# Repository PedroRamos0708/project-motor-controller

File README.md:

# Projeto de Controle com Microcontrolador

## Descrição
Este projeto foi desenvolvido como parte de um desafio de hardware.
O objetivo é criar um sistema embarcado capaz de:
* Receber um sinal externo de 12 V ativo em nível baixo.
* Acionar um motor DC 5 V / 1 A por 10 segundos.
* Enviar mensagens de status via UART RS232.
* Ser alimentado por uma fonte de 9 a 24 VDC, com proteções contra inversão de polaridade e surtos.

## Especificações de Hardware
* Microcontrolador: ATmega328P + botão de reset.
* Fonte de alimentação: regulador LM2596 (9–24 VDC para 5 V).
* Motor: 5 V / 1 A, acionado via MOSFET canal N, com fusível de proteção.
* Proteções:
  * Fusível resetável (PTC).
  * Diodo Schottky (SS34).
  * Diodo TVS (SMBJ33A).
* Interface de entrada: optoacoplador para isolamento do sinal de 12 V.
* Comunicação serial: MAX3232 para RS232.
* Sinalização de placa energizada: LED

## Firmware
O firmware em C/C++ (pronto para compilação no ARDUINO IDE) realiza:
1. Leitura do sinal externo via optoacoplador.
2. Acionamento do motor por 10 segundos.
3. Envio de mensagens de status na UART.

## Arquivos Gerados
* Esquemático em PDF.
* PCB desenhada no KiCad 9.
* Arquivos Gerber e Drill files para fabricação.
* Pick and Place (PnP) para montagem.
* BOM (Bill of Materials) para compra dos componentes.
* Arquivos de projeto editáveis da placa e esquematico (.kicad_pcd e _sch)

## Como usar
1. Alimente a placa com 9 a 24 VDC no conector J1 (pino interno VCC e externo GND) através de fonte externa;
2. Conecte o sinal externo de 12 V no borne J3 (pino 1 : GND, pino 2 : 12V) para habilitação do motor;
3. Conecte o motor DC 5 V / 1 A no borne J4 (pino 1 : +, pino 2 : GND);
4. Utilize a porta RS232 (Conector db9 J2) para monitorar as mensagens do sistema.

## Tecnologias Utilizadas
* KiCad 9 → desenvolvimento do esquemático e PCB.
* Arduino IDE → programação do microcontrolador.

## Autor
Projeto desenvolvido por Pedro Henrique Ramos, Engenheiro de Controle e Automação e técnico em eletroeletrônica.

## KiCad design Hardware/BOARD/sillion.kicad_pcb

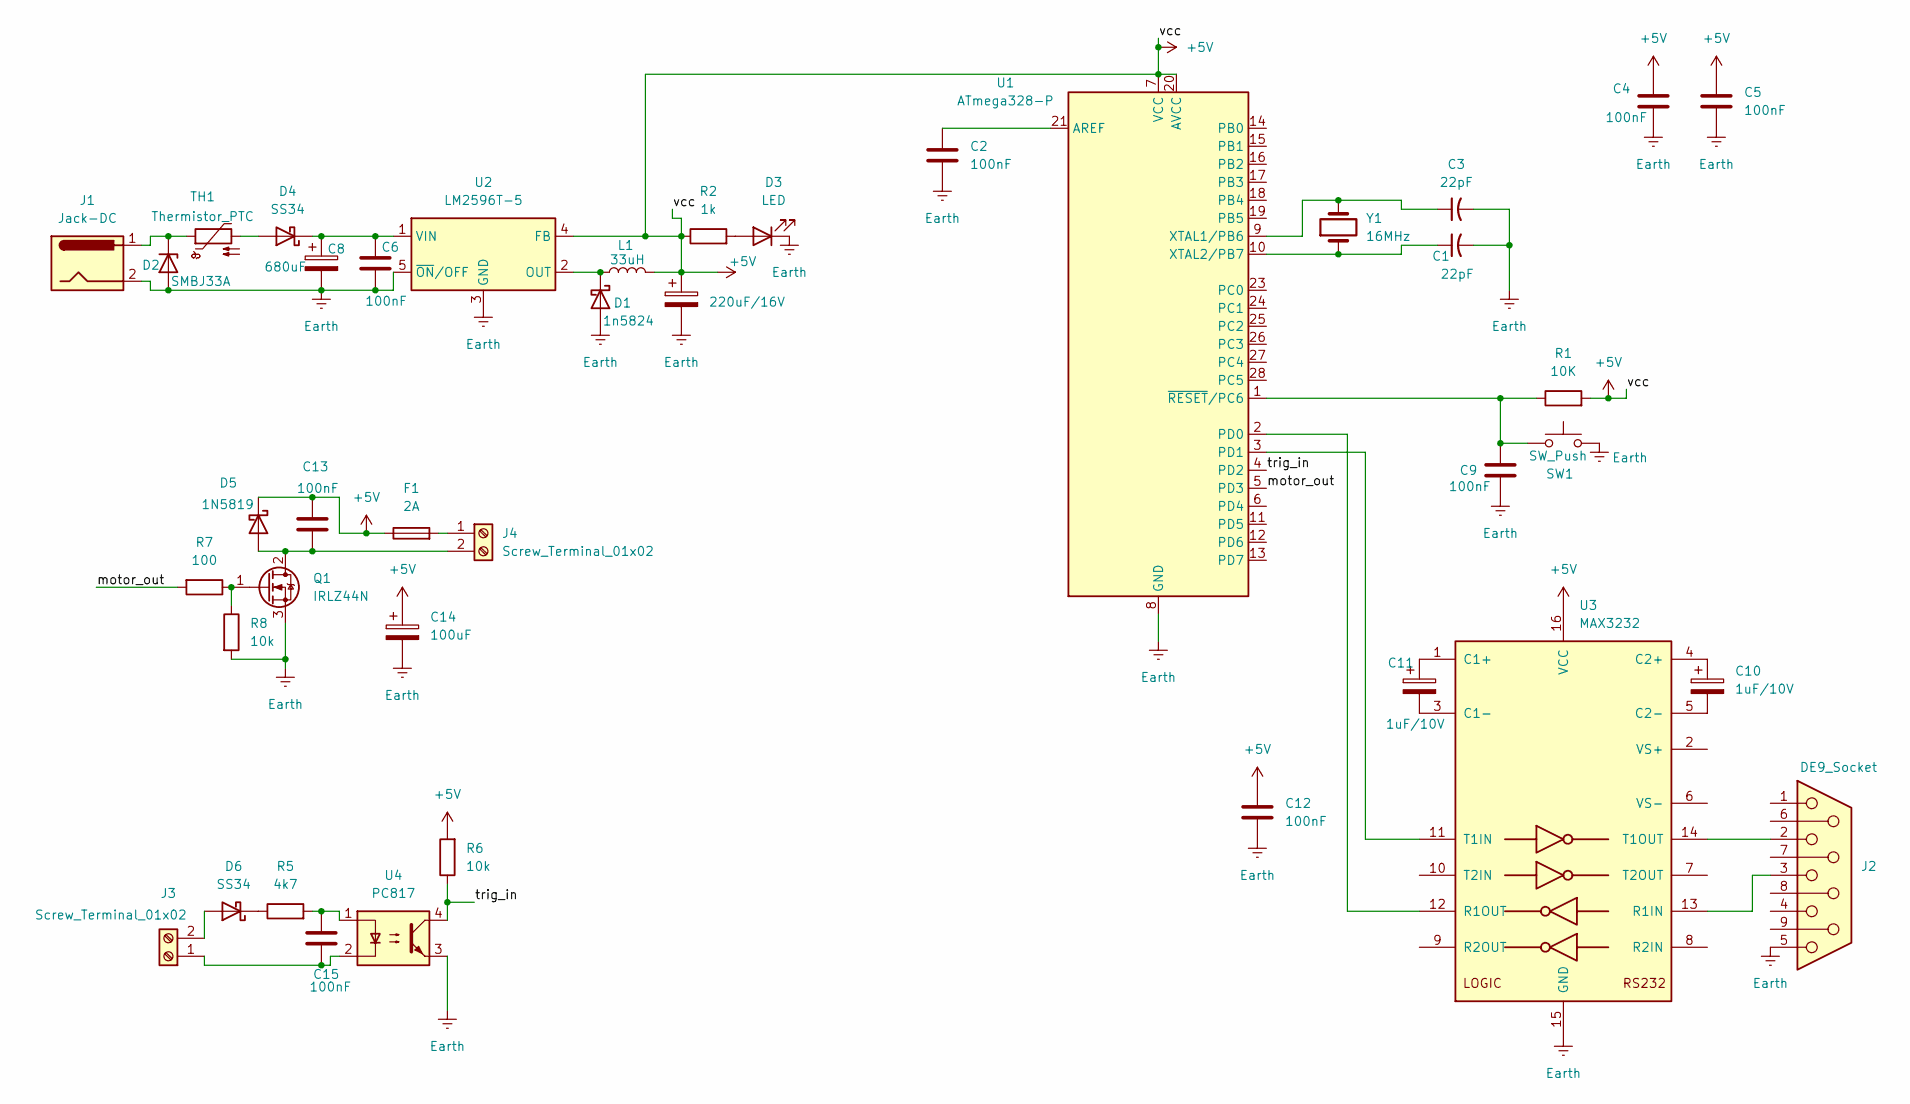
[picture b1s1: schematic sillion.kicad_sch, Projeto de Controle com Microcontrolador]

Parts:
C1, C3: 22pF; C_Disc_D4.3mm_W1.9mm_P5.00mm
C2, C4, C5, C6, C9, C12, C13, C15: 100nF; C_Disc_D4.3mm_W1.9mm_P5.00mm
C7: 220uF/16V; CP_Radial_D8.0mm_P5.00mm
C8: 680uF; CP_Radial_D13.0mm_P7.50mm
C10, C11: 1uF/10V; C_0805_2012Metric
C14: 100uF; CP_Radial_D5.0mm_P2.50mm
D1: 1n5824; TO-220-2_Vertical
D2: SMBJ33A; D_SMB
D3: LED; LED_D5.0mm
D4, D6: SS34; D_SMA
D5: 1N5819; D_DO-41_SOD81_P10.16mm_Horizontal
F1: 2A; Fuseholder_Clip-5x20mm_Bel_FC-203-22_Lateral_P17.80x5.00mm_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
J1: Jack-DC; BarrelJack_Horizontal
J2: DE9_Socket; DSUB-9_Socket_Horizontal_P2.77x2.84mm_EdgePinOffset4.94mm_H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
J3, J4: Screw_Terminal_01x02; TerminalBlock_Altech_AK300-2_P5.00mm
L1: 33uH; L_Radial_D12.5mm_P7.00mm_Fastron_09HCP
Q1: IRLZ44N; TO-220-3_Vertical
R1: 10K; R_Axial_DIN0207_L6.3mm_D2.5mm_P10.16mm_Horizontal
R2: 1k; R_Axial_DIN0207_L6.3mm_D2.5mm_P10.16mm_Horizontal
R5: 4k7; R_Axial_DIN0207_L6.3mm_D2.5mm_P10.16mm_Horizontal
R6, R8: 10k; R_Axial_DIN0207_L6.3mm_D2.5mm_P10.16mm_Horizontal
R7: 100; R_Axial_DIN0207_L6.3mm_D2.5mm_P10.16mm_Horizontal
SW1: SW_Push; SW_PUSH_6mm_H5mm
TH1: Thermistor_PTC; Fuse_BelFuse_0ZRE0025FF_L9.6mm_W3.8mm
U1: ATmega328-P; DIP-28_W7.62mm
U2: LM2596T-5; TO-220-5_P3.4x3.7mm_StaggerOdd_Lead3.8mm_Vertical
U3: MAX3232; JEITA_SOIC-16_3.9x9.9mm_P1.27mm
U4: PC817; DIP-4_W7.62mm
Y1: 16MHz; Crystal_HC49-4H_Vertical

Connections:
+5V: C4.1, C5.1, C7.1, C12.1, C13.1, C14.1, D5.1 (K), F1.1, L1.2, R1.2, R2.1, R6.2, U1.7 (VCC), U1.20 (AVCC), U2.4 (FB), U3.16 (VCC)
/motor_out: R7.2, U1.5 (PD3)
/trig_in: R6.1, U1.4 (PD2), U4.4
Earth: C1.2, C2.2, C3.2, C4.2, C5.2, C6.2, C7.2, C8.2, C9.2, C12.2, C14.2, D1.2 (A), D2.2 (A), D3.1 (K), J1.2, J2.5, Q1.3 (S), R8.2, SW1.2, U1.8 (GND), U1.22 (GND), U2.3 (GND), U2.5 (~ON/OFF), U3.15 (GND), U4.3
unnamed: C15.1, R5.2, U4.1
unnamed: D1.1 (K), L1.1, U2.2 (OUT)
unnamed: D2.1 (K), J1.1, TH1.1
unnamed: D3.2 (A), R2.2
unnamed: D4.2 (A), TH1.2
unnamed: C6.1, C8.1, D4.1 (K), U2.1 (VIN)
unnamed: C13.2, D5.2 (A), J4.2, Q1.2 (D)
unnamed: D6.2 (A), J3.2
unnamed: D6.1 (K), R5.1
unnamed: C15.2, J3.1, U4.2
unnamed: F1.2, J4.1
unnamed: Q1.1 (G), R7.1, R8.1
unnamed: C2.1, U1.21 (AREF)
unnamed: U1.2 (PD0), U3.12 (R1OUT)
unnamed: U1.3 (PD1), U3.11 (T1IN)
unnamed: C3.1, U1.9 (XTAL1/PB6), Y1.2
unnamed: C1.1, U1.10 (XTAL2/PB7), Y1.1
unnamed: C9.1, R1.1, SW1.1, U1.1 (~RESET/PC6)
unnamed: C11.1, U3.1 (C1+)
unnamed: C11.2, U3.3 (C1-)
unnamed: C10.1, U3.4 (C2+)
unnamed: C10.2, U3.5 (C2-)
unnamed: J2.3, U3.13 (R1IN)
unnamed: J2.2, U3.14 (T1OUT)

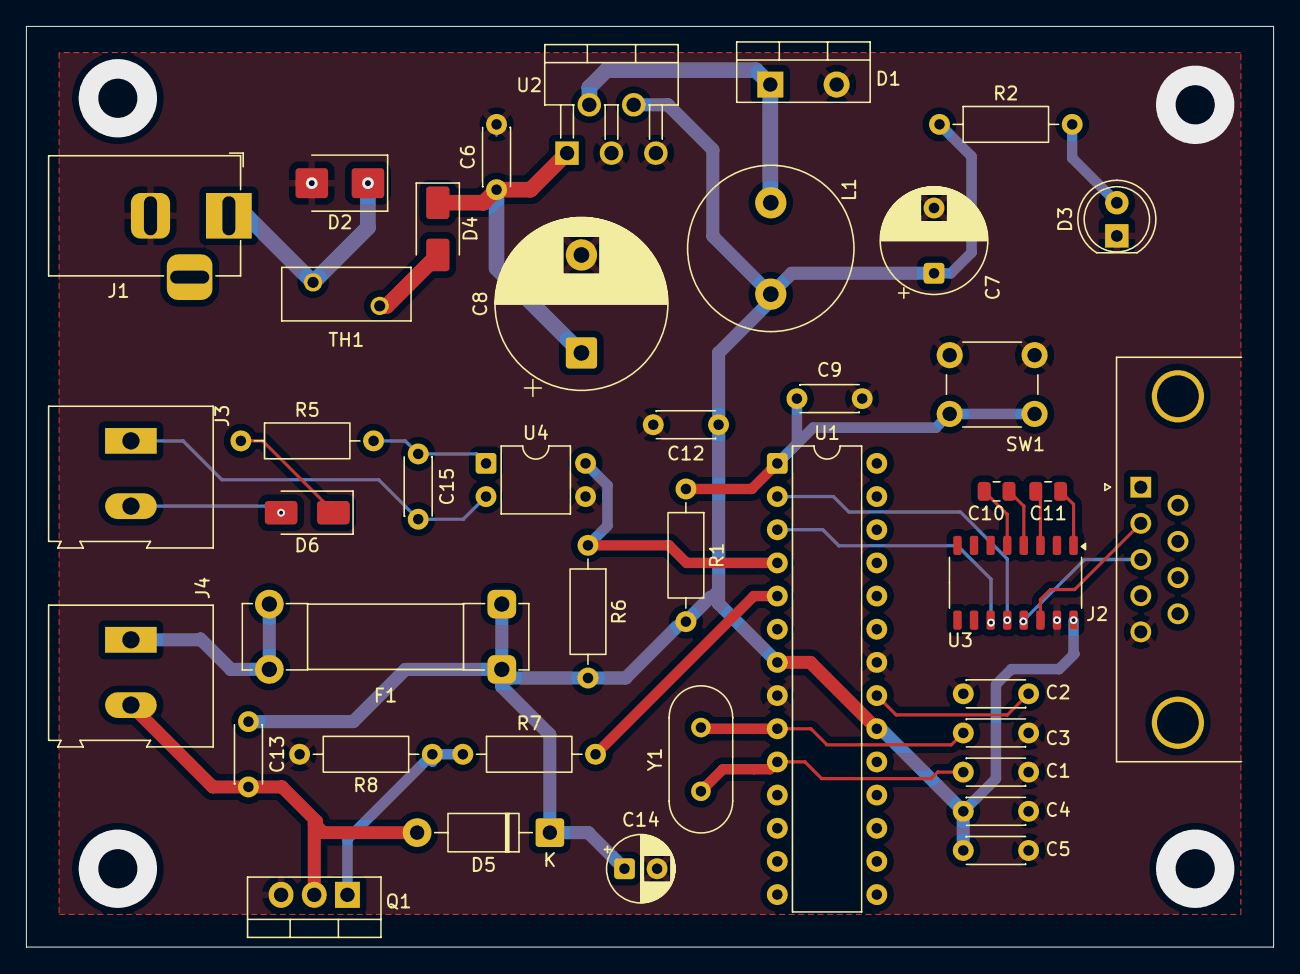
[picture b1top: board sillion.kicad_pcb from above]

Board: 2 copper layers, 95.5 x 70.5 mm, 41 parts (0 on the bottom side), 28 nets.

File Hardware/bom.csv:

"Reference","Qty","Value","DNP","Exclude from BOM","Exclude from Board","Footprint","Datasheet"
"C1,C3","2","22pF","","","","Capacitor_THT:C_Disc_D4.3mm_W1.9mm_P5.00mm",""
"C2,C4,C5,C6,C9,C12,C13,C15","8","100nF","","","","Capacitor_THT:C_Disc_D4.3mm_W1.9mm_P5.00mm","~"
"C7","1","220uF/16V","","","","Capacitor_THT:CP_Radial_D8.0mm_P5.00mm","~"
"C8","1","680uF","","","","Capacitor_THT:CP_Radial_D13.0mm_P7.50mm","~"
"C10,C11","2","1uF/10V","","","","Capacitor_SMD:C_0805_2012Metric","~"
"C14","1","100uF","","","","Capacitor_THT:CP_Radial_D5.0mm_P2.50mm","~"
"D1","1","1n5824","","","","Package_TO_SOT_THT:TO-220-2_Vertical","~"
"D2","1","SMBJ33A","","","","Diode_SMD:D_SMB","~"
"D3","1","LED","","","","LED_THT:LED_D5.0mm","~"
"D4,D6","2","SS34","","","","Diode_SMD:D_SMA","https://www.vishay.com/docs/88751/ss32.pdf"
"D5","1","1N5819","","","","Diode_THT:D_DO-41_SOD81_P10.16mm_Horizontal","http://www.vishay.com/docs/88525/1n5817.pdf"
"F1","1","2A","","","","Fuse:Fuseholder_Clip-5x20mm_Bel_FC-203-22_Lateral_P17.80x5.00mm_D1.17mm_Horizontal","~"
"J1","1","Jack-DC","","","","Connector_BarrelJack:BarrelJack_Horizontal","~"
"J2","1","DE9_Socket","","","","Connector_Dsub:DSUB-9_Socket_Horizontal_P2.77x2.84mm_EdgePinOffset4.94mm_Housed_MountingHolesOffset4.94mm","~"
"J3,J4","2","Screw_Terminal_01x02","","","","TerminalBlock:TerminalBlock_Altech_AK300-2_P5.00mm","~"
"L1","1","33uH","","","","Inductor_THT:L_Radial_D12.5mm_P7.00mm_Fastron_09HCP","~"
"Q1","1","IRLZ44N","","","","Package_TO_SOT_THT:TO-220-3_Vertical","http://www.irf.com/product-info/datasheets/data/irlz44n.pdf"
"R1","1","10K","","","","Resistor_THT:R_Axial_DIN0207_L6.3mm_D2.5mm_P10.16mm_Horizontal","~"
"R2","1","1k","","","","Resistor_THT:R_Axial_DIN0207_L6.3mm_D2.5mm_P10.16mm_Horizontal","~"
"R5","1","4k7","","","","Resistor_THT:R_Axial_DIN0207_L6.3mm_D2.5mm_P10.16mm_Horizontal","~"
"R6,R8","2","10k","","","","Resistor_THT:R_Axial_DIN0207_L6.3mm_D2.5mm_P10.16mm_Horizontal","~"
"R7","1","100","","","","Resistor_THT:R_Axial_DIN0207_L6.3mm_D2.5mm_P10.16mm_Horizontal","~"
"SW1","1","SW_Push","","","","Button_Switch_THT:SW_PUSH_6mm_H5mm","~"
"TH1","1","Thermistor_PTC","","","","Fuse:Fuse_BelFuse_0ZRE0025FF_L9.6mm_W3.8mm","~"
"U1","1","ATmega328-P","","","","Package_DIP:DIP-28_W7.62mm","http://ww1.microchip.com/downloads/en/DeviceDoc/ATmega328_P%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"
"U2","1","LM2596T-5","","","","Package_TO_SOT_THT:TO-220-5_P3.4x3.7mm_StaggerOdd_Lead3.8mm_Vertical","http://www.ti.com/lit/ds/symlink/lm2596.pdf"
"U3","1","MAX3232","","","","Package_SO:JEITA_SOIC-16_3.9x9.9mm_P1.27mm","https://datasheets.maximintegrated.com/en/ds/MAX3222-MAX3241.pdf"
"U4","1","PC817","","","","Package_DIP:DIP-4_W7.62mm","http://www.soselectronic.cz/a_info/resource/d/pc817.pdf"
"Y1","1","16MHz","","","","Crystal:Crystal_HC49-4H_Vertical","~"

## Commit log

2025-09-03 README.md
